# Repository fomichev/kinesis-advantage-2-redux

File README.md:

# Kinesis Advantage 2 PR2024 Redux

## Motivation

I've been an avid Kinesis Advantage 2 (KA2) user for years, but recently
I felt the urge to explore alternative switch options beyond the classic
Cherry MX. Unfortunately, Kinesis stopped offering replacement PCBs around
2022-2023, and my soldering skills aren't quite up to the challenge of
a DIY swap.

That's why this project exists: to completely rewire your KA2 with
custom-designed PCBs, giving you the flexibility to use any switches you
desire without having to deal with the complexity of preserving or
desoldering the original boards. This build leverages the powerful QMK
firmware and RP2040 microcontroller, ensuring a seamless and customizable
experience.

# Ordering PCBs

I've been using [JLCPCB](https://jlcpcb.com). All PCBs are reversible,
so ordering 5x each (minimum order amount) will be enough to rewire
2 keyboards. For the main PCB and the thumb clusters - use the default settings.
For the hand PCB (the one that looks funny and needs to be flexible),
make sure to select 6mm thickness. The gerbers are under `gerbers/` directory.

Note, stock Kinesis PCB is 4mm thick, but 6mm seems to be working fine as
well. Ordering 4mm is 5x more expensive than 6mm. The fit is not 100%
correct, but there is enough slack to make it work.

As of Sep 2024, the prices are (ignoring the shipping cost):
- $6.80 5pcs thumb PCB
- $7.70 5pcs main PCB
- $10.10 5pcs 6mm hand PCB

# BOM

- $1.78 10cm XH2.54 connector cable 5P Double head https://www.aliexpress.us/item/2255800512569466.html
- $1.87 10cm XH2.54 connector cable 6P Double head https://www.aliexpress.us/item/2255800512569466.html
- $2.06 10cm XH2.54 connector cable 7P Double head https://www.aliexpress.us/item/2255800512569466.html
- $1.89 50Pcs XH2.54 ping header 5Pin https://www.aliexpress.us/item/2251832515485565.html
- $2.19 50Pcs XH2.54 ping header 6Pin https://www.aliexpress.us/item/2251832515485565.html
- $2.17 50Pcs XH2.54 ping header 7Pin https://www.aliexpress.us/item/2251832515485565.html
- $1.90 RP2040 https://www.aliexpress.us/item/3256803184741525.html
- $1.04 100pcs 1N4148 diodes https://www.aliexpress.us/item/2255799955957794.html
- 68 MX-style switches

# Build Guide

Start with the disassembly. Remove everything except the top row (which
is being reused as is) and install the new switches.

## Hands

1. Solder diodes (pay attention to the orientation: diodes have a black line
on one side that should align with the line on the pcb) and connectors
(orientation matters for these too; should be easy to deduce the correct
one from the pcb markings).

2. Install and solder the middle row. This should leave you enough wiggle
room to fit the rest.

3. Solder the rest of the switches.

## Thumbs

1. Solder diodes and connectors.

2. Solder the switches.

## Main PCB

1. Solder PR2040 and connectors. Pay attention to the correct orientation
of the connectors.

## Assemble

Assemble all the pieces.

And attach the cables.

# Software

See [my QMK fork](http://github.com/fomichev/qmk_firmware) for the changes
required:

```
git clone https://github.com/fomichev/qmk_firmware.git
qmk flash -kb kinesis/redux -km fomichev
```

# Keyboard Matrix

The keyboard matrix has nothing in common with the stock Kinesis one (except
functional keys which are reused), so other custom controller won't fit.
It is a bit unconventional due to reverse PCB design.

```
  |     0 |     1 |    2 |    3 |    4 |   5 |   6 |     7 |    8 |    9 |  10 |    11 |  12 |   13 |   14
--+-------+-------+------+------+------+-----+-----+-------+------+------+-----+-------+-----+------+-----
0 |    =  |     1 |    2 |    3 |    4 |   5 |   6 |     7 |    8 |    9 |   0 |     - | ESC |   F1 |   F2
1 |  TAB  |     Q |    W |    E |    R |   T |   Y |     U |    I |    O |   P |     \ |  F3 |   F4 |   F5
2 | CLOCK |     A |    S |    D |    F |   G |   H |     J |    K |    L |   ; |     ' |  F6 |   F7 |   F8
3 | SHIFT |     Z |    X |    C |    V |   B |   N |     M |    < |    > |   ? | SHIFT |  F9 |  F10 |  F11
4 |       |     ` |    | | LEFT | RGHT |     |     |    UP |   DN |    { |   } |       | F12 | PRSC |  SRL
5 |  LALT | LCTRL | HOME |  DEL | BSPC | END | GUI | RCTRL | PGUP | ENTR | SPC |  PGDN | PAU | KEYP | PRGM
```

# Future Design

Potential future design might attempt to reuse FPC cables that come with
the keyboard and use Molex [0039532135 CONN FFC VERT 13POS 1.25MM PCB](https://www.digikey.com/en/products/detail/molex/0039532135/3160262)
connectors. This should make the BOM smaller and slightly cheaper. But
making everything reversible might be a bit of a PITA.

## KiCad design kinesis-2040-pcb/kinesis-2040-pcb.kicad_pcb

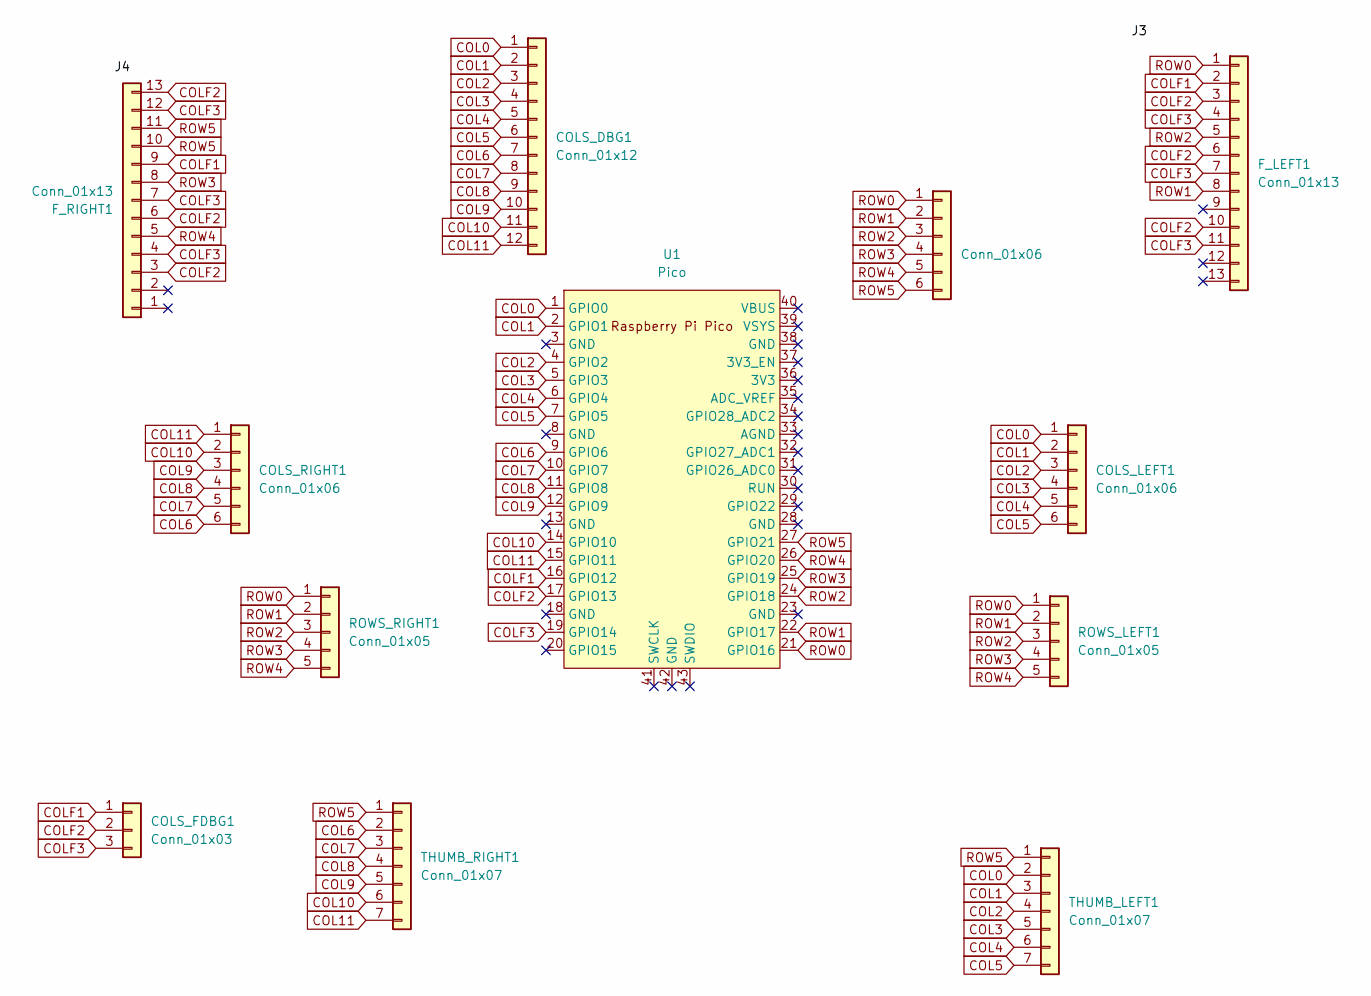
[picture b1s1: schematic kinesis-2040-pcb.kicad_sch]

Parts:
COLS_DBG1: Conn_01x12; PinHeader_1x12_P2.54mm_Vertical
COLS_FDBG1: Conn_01x03; PinHeader_1x03_P2.54mm_Vertical
COLS_LEFT1: Conn_01x06; JST_XH_B6B-XH-A_1x06_P2.50mm_Vertical
COLS_RIGHT1: Conn_01x06; JST_XH_B6B-XH-A_1x06_P2.50mm_Vertical
F_LEFT1: Conn_01x13; 39-53-2135
F_RIGHT1: Conn_01x13; 39-53-2135
ROWS_DBG2: Conn_01x06; PinHeader_1x06_P2.54mm_Vertical
ROWS_LEFT1: Conn_01x05; JST_XH_B5B-XH-A_1x05_P2.50mm_Vertical
ROWS_RIGHT1: Conn_01x05; JST_XH_B5B-XH-A_1x05_P2.50mm_Vertical
THUMB_LEFT1: Conn_01x07; JST_XH_B7B-XH-A_1x07_P2.50mm_Vertical
THUMB_RIGHT1: Conn_01x07; JST_XH_B7B-XH-A_1x07_P2.50mm_Vertical
U1: Pico; RPi_Pico_SMD_TH

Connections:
COL0: COLS_DBG1.1, COLS_LEFT1.1, THUMB_LEFT1.2, U1.1 (GPIO0)
COL1: COLS_DBG1.2, COLS_LEFT1.2, THUMB_LEFT1.3, U1.2 (GPIO1)
COL2: COLS_DBG1.3, COLS_LEFT1.3, THUMB_LEFT1.4, U1.4 (GPIO2)
COL3: COLS_DBG1.4, COLS_LEFT1.4, THUMB_LEFT1.5, U1.5 (GPIO3)
COL4: COLS_DBG1.5, COLS_LEFT1.5, THUMB_LEFT1.6, U1.6 (GPIO4)
COL5: COLS_DBG1.6, COLS_LEFT1.6, THUMB_LEFT1.7, U1.7 (GPIO5)
COL6: COLS_DBG1.7, COLS_RIGHT1.6, THUMB_RIGHT1.2, U1.9 (GPIO6)
COL7: COLS_DBG1.8, COLS_RIGHT1.5, THUMB_RIGHT1.3, U1.10 (GPIO7)
COL8: COLS_DBG1.9, COLS_RIGHT1.4, THUMB_RIGHT1.4, U1.11 (GPIO8)
COL9: COLS_DBG1.10, COLS_RIGHT1.3, THUMB_RIGHT1.5, U1.12 (GPIO9)
COL10: COLS_DBG1.11, COLS_RIGHT1.2, THUMB_RIGHT1.6, U1.14 (GPIO10)
COL11: COLS_DBG1.12, COLS_RIGHT1.1, THUMB_RIGHT1.7, U1.15 (GPIO11)
COLF1: COLS_FDBG1.1, F_LEFT1.2, F_RIGHT1.9, U1.16 (GPIO12)
COLF2: COLS_FDBG1.2, F_LEFT1.3, F_LEFT1.6, F_LEFT1.10, F_RIGHT1.3, F_RIGHT1.6, F_RIGHT1.13, U1.17 (GPIO13)
COLF3: COLS_FDBG1.3, F_LEFT1.4, F_LEFT1.7, F_LEFT1.11, F_RIGHT1.4, F_RIGHT1.7, F_RIGHT1.12, U1.19 (GPIO14)
ROW0: F_LEFT1.1, ROWS_DBG2.1, ROWS_LEFT1.1, ROWS_RIGHT1.1, U1.21 (GPIO16)
ROW1: F_LEFT1.8, ROWS_DBG2.2, ROWS_LEFT1.2, ROWS_RIGHT1.2, U1.22 (GPIO17)
ROW2: F_LEFT1.5, ROWS_DBG2.3, ROWS_LEFT1.3, ROWS_RIGHT1.3, U1.24 (GPIO18)
ROW3: F_RIGHT1.8, ROWS_DBG2.4, ROWS_LEFT1.4, ROWS_RIGHT1.4, U1.25 (GPIO19)
ROW4: F_RIGHT1.5, ROWS_DBG2.5, ROWS_LEFT1.5, ROWS_RIGHT1.5, U1.26 (GPIO20)
ROW5: F_RIGHT1.10, F_RIGHT1.11, ROWS_DBG2.6, THUMB_LEFT1.1, THUMB_RIGHT1.1, U1.27 (GPIO21)

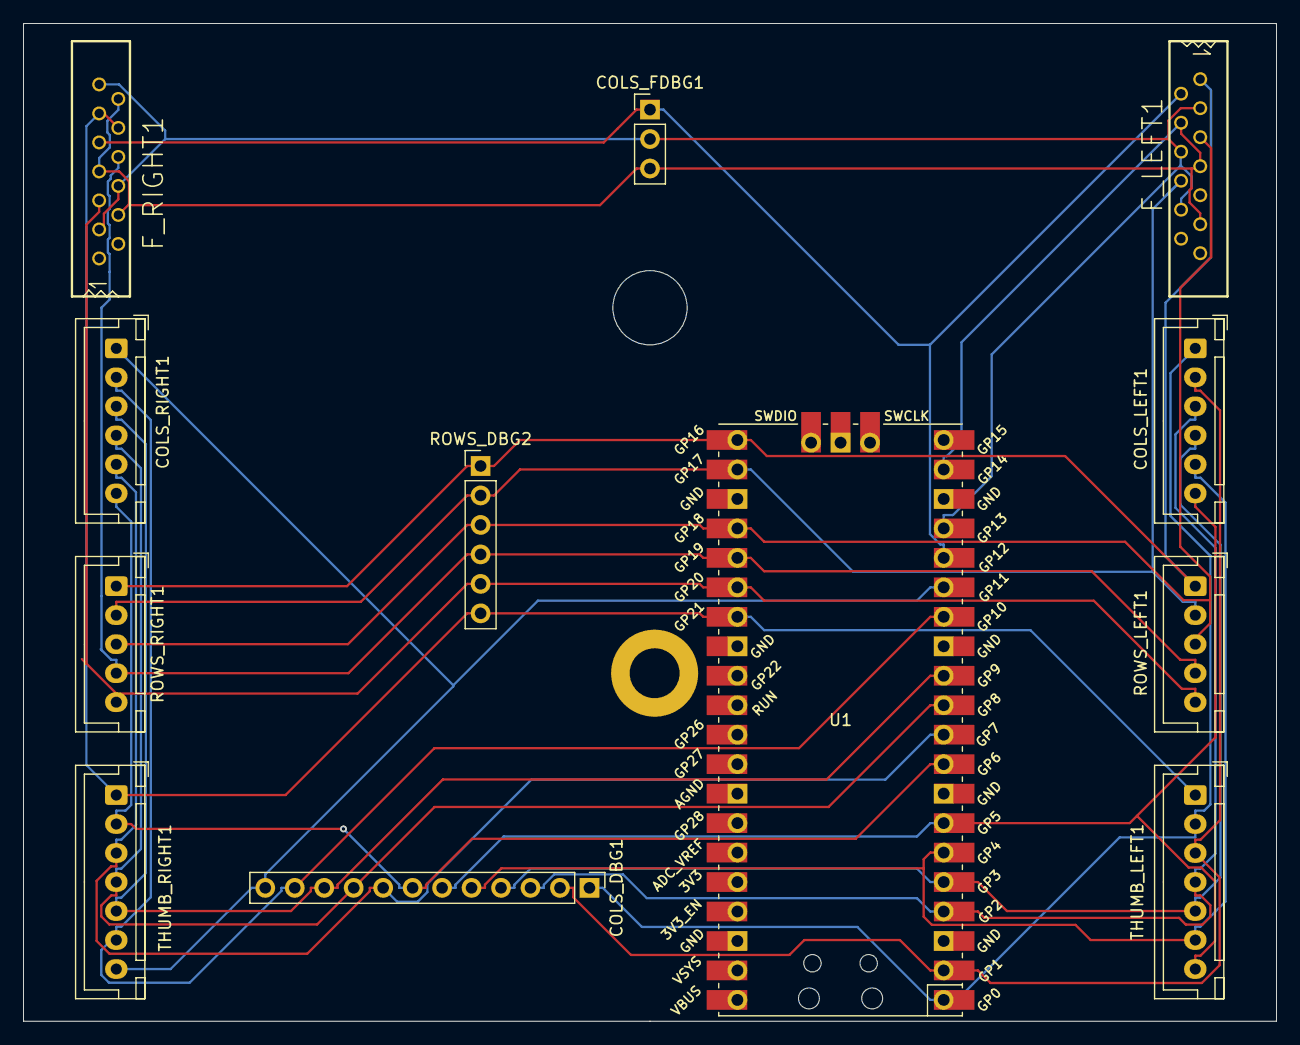
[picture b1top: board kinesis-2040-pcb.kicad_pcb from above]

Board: 2 copper layers, 108.0 x 86.0 mm, 13 parts (0 on the bottom side), 21 nets.

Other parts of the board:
H1: MountingHole_6.4mm_M6_DIN965
